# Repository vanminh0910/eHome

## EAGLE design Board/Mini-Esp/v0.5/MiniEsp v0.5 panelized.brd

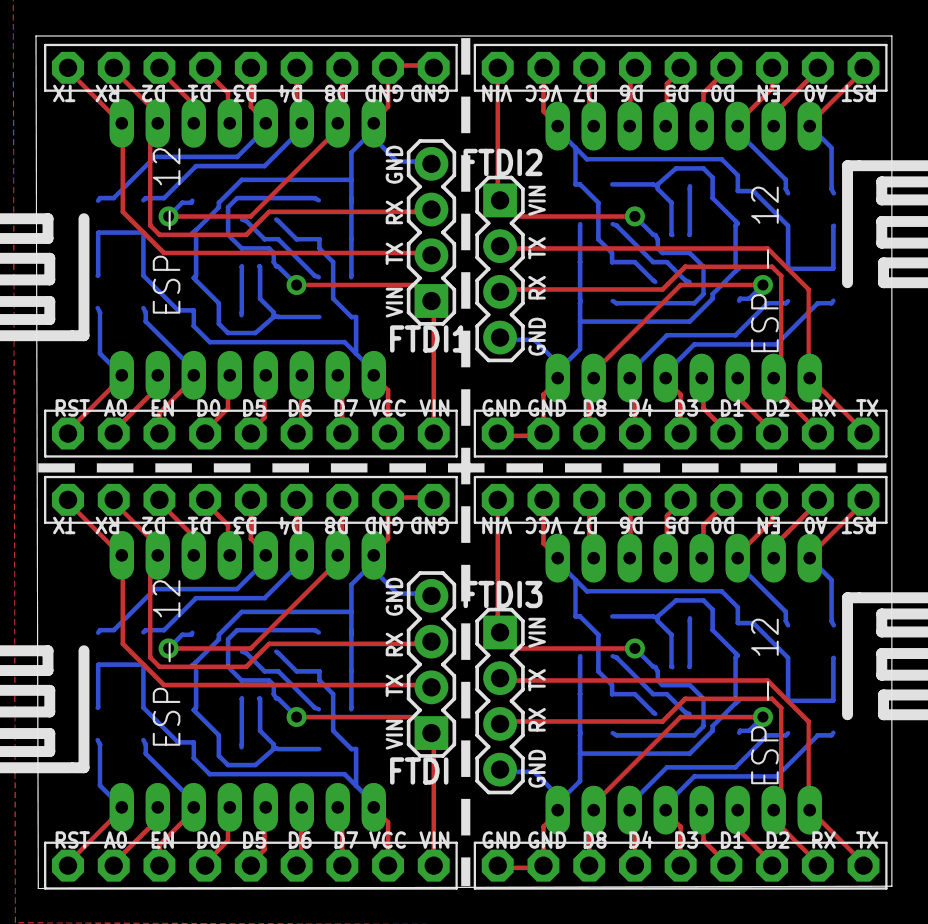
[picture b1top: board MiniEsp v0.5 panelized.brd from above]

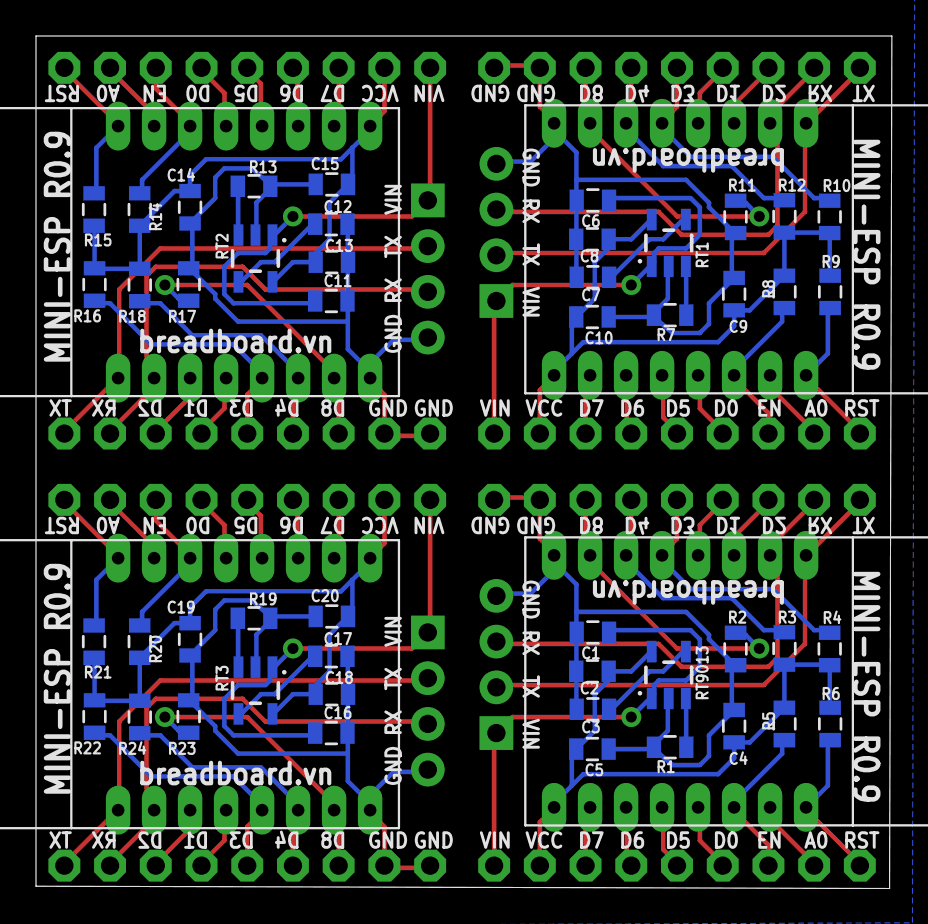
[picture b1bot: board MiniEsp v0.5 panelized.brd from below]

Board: 2 copper layers, 47.5 x 47.4 mm, 64 parts (48 on the bottom side), 76 nets.

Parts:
C1, C2, C6, C8, C11, C13, C16, C18: 1uF; 0805
C3, C7, C12, C17: 22nF; 0805
C4, C9, C14, C19: 10uF; 0805
C5, C10, C15, C20: 100nF; 0805
FTDI, FTDI1, FTDI2, FTDI3: 1X04
JP1, JP2, JP3, JP4, JP5, JP6, JP7, JP8: 1X09-BIG
R1, R7, R13, R19: 100K; 0805
R2, R3, R4, R5, R6, R8, R9, R10, R11, R12, R14, R15, R16, R17, R18, R20, R21, R22, R23, R24: 10K; 0805
RT1, RT2, RT3, RT9013: 3.3V/150mA; SOT23-5
U1, U2, U3, U4: ESP12

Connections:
A0: JP2.8, U2.ADC
A1: JP4.8, U1.ADC
A2: JP6.8, U3.ADC
A3: JP8.8, U4.ADC
BP: C3.1, RT9013.4
BP1: C7.1, RT1.4
BP2: C12.1, RT2.4
BP3: C17.1, RT3.4
D0: JP2.6, U2.GPIO16
D1: JP1.4, U2.GPIO5
D2: JP1.3, U2.GPIO4
D3: JP1.5, R4.1, U2.GPIO0
D4: JP1.6, R3.1, U2.GPIO2
D5: JP2.5, U2.GPIO14
D6: JP2.4, U2.GPIO12
D7: JP2.3, U2.GPIO13
D8: JP1.7, R2.1, U2.GPIO15
D9: JP3.3, U1.GPIO4
D10: JP3.4, U1.GPIO5
D11: JP3.5, R10.1, U1.GPIO0
D12: JP3.6, R12.1, U1.GPIO2
D13: JP3.7, R11.1, U1.GPIO15
D14: JP4.6, U1.GPIO16
D15: JP4.5, U1.GPIO14
D16: JP4.4, U1.GPIO12
D17: JP4.3, U1.GPIO13
D18: JP5.3, U3.GPIO4
D19: JP5.4, U3.GPIO5
D20: JP5.5, R16.1, U3.GPIO0
D21: JP5.6, R18.1, U3.GPIO2
D22: JP5.7, R17.1, U3.GPIO15
D23: JP6.6, U3.GPIO16
D24: JP6.5, U3.GPIO14
D25: JP6.4, U3.GPIO12
D26: JP6.3, U3.GPIO13
D27: JP7.3, U4.GPIO4
D28: JP7.4, U4.GPIO5
D29: JP7.5, R22.1, U4.GPIO0
D30: JP7.6, R24.1, U4.GPIO2
D31: JP7.7, R23.1, U4.GPIO15
D32: JP8.6, U4.GPIO16
D33: JP8.5, U4.GPIO14
D34: JP8.4, U4.GPIO12
D35: JP8.3, U4.GPIO13
EN: JP2.7, R5.1, U2.CH_PD
EN1: JP4.7, R8.1, U1.CH_PD
EN2: JP6.7, R14.1, U3.CH_PD
EN3: JP8.7, R20.1, U4.CH_PD
GND: C1.2, C2.2, C3.2, C4.2, C5.2, FTDI.4, JP1.8, JP1.9, R1.2, R2.2, RT9013.2, U2.GND
GND1: C6.2, C7.2, C8.2, C9.2, C10.2, FTDI1.4, JP3.8, JP3.9, R7.2, R11.2, RT1.2, U1.GND
GND2: C11.2, C12.2, C13.2, C14.2, C15.2, FTDI2.4, JP5.8, JP5.9, R13.2, R17.2, RT2.2, U3.GND
GND3: C16.2, C17.2, C18.2, C19.2, C20.2, FTDI3.4, JP7.8, JP7.9, R19.2, R23.2, RT3.2, U4.GND
LDO_EN: R1.1, RT9013.3
LDO_EN1: R7.1, RT1.3
LDO_EN2: R13.1, RT2.3
LDO_EN3: R19.1, RT3.3
RST: JP2.9, R6.1, U2.RESET
RST1: JP4.9, R9.1, U1.RESET
RST2: JP6.9, R15.1, U3.RESET
RST3: JP8.9, R21.1, U4.RESET
RX: FTDI.3, JP1.2, U2.RX
RX1: FTDI1.3, JP3.2, U1.RX
RX2: FTDI2.3, JP5.2, U3.RX
RX3: FTDI3.3, JP7.2, U4.RX
TX: FTDI.2, JP1.1, U2.TX
TX1: FTDI1.2, JP3.1, U1.TX
TX2: FTDI2.2, JP5.1, U3.TX
TX3: FTDI3.2, JP7.1, U4.TX
VCC: C2.1, C4.1, C5.1, JP2.2, R3.2, R4.2, R5.2, R6.2, RT9013.5, U2.VCC
VCC1: C8.1, C9.1, C10.1, JP4.2, R8.2, R9.2, R10.2, R12.2, RT1.5, U1.VCC
VCC2: C13.1, C14.1, C15.1, JP6.2, R14.2, R15.2, R16.2, R18.2, RT2.5, U3.VCC
VCC3: C18.1, C19.1, C20.1, JP8.2, R20.2, R21.2, R22.2, R24.2, RT3.5, U4.VCC
VIN: C1.1, FTDI.1, JP2.1, RT9013.1
VIN1: C6.1, FTDI1.1, JP4.1, RT1.1
VIN2: C11.1, FTDI2.1, JP6.1, RT2.1
VIN3: C16.1, FTDI3.1, JP8.1, RT3.1

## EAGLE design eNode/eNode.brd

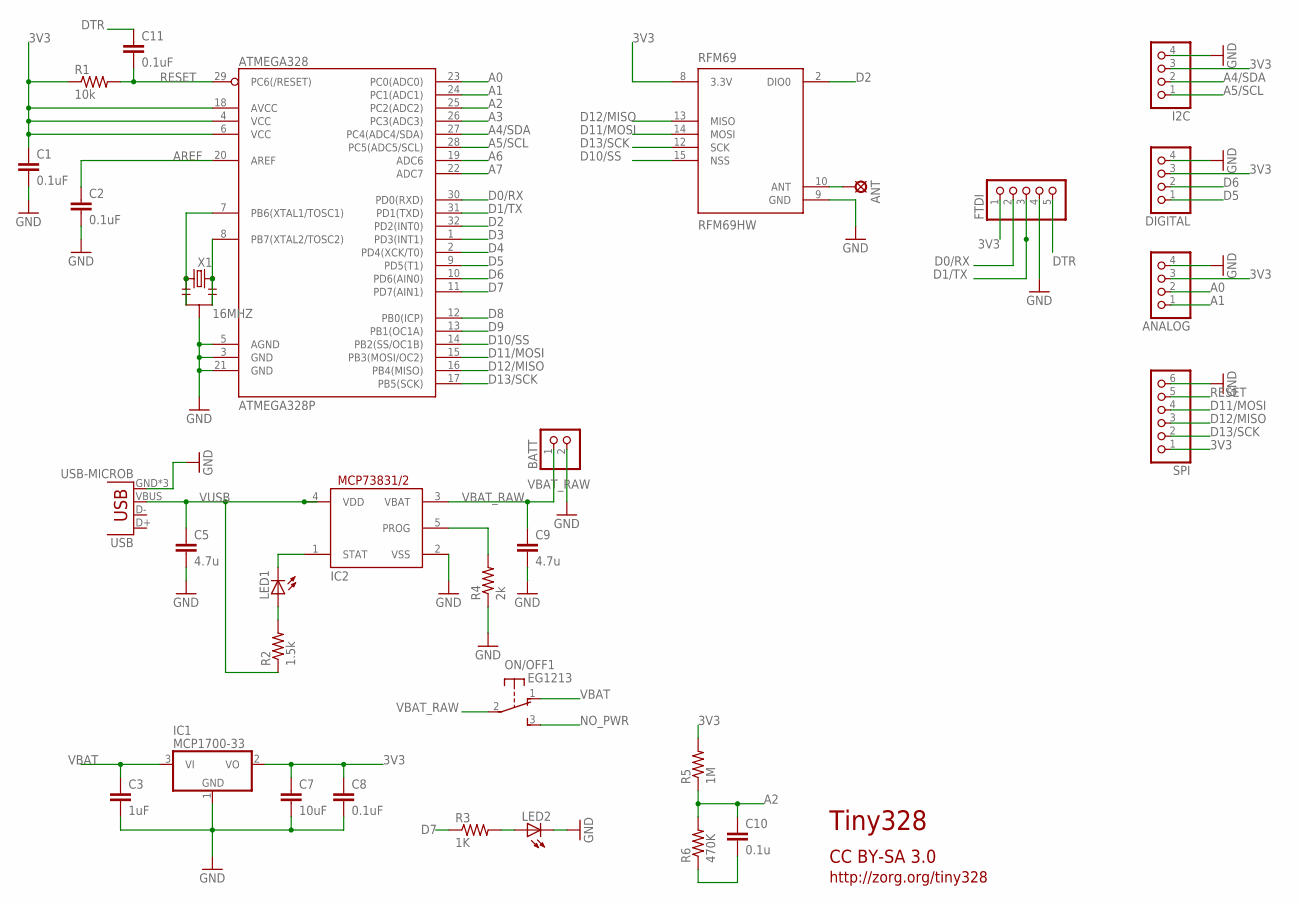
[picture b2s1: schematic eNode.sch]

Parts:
ANALOG: PINHD-1X4; 1X04
ANT: LSP10
ATMEGA328P: ATMEGA328; TQFP32-08
BATT: PINHD-1X2; 1X02
C1, C2, C8, C11: 0.1uF; 0603-CAP
C3: 1uF; 0603-CAP
C5, C9: 4.7u; 0603-CAP
C7: 10uF; 0603-CAP
C10: 0.1u; 0603-CAP
DIGITAL: PINHD-1X4; 1X04
FTDI: PINHD-1X5; 1X05
I2C: PINHD-1X4; 1X04
IC1: MCP1700-33; SOT23
IC2: MCP73831/OT; SOT23-5L
LED1, LED2: LEDCHIPLED_0603; CHIPLED_0603
ON/OFF: EG1213
R1: 10k; 0603-RES
R2: 1.5k; 0603-RES
R3: 1K; 0603-RES
R4: 2k; 0603-RES
R5: 1M; 0603-RES
R6: 470K; 0603-RES
RFM69: RFM69HW; RFM69W-XXXS2
SPI: PINHD-1X6; 1X06
USB: USB-MICROB
X1: 16MHZ; RESONATOR-SMD

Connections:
3V3: ANALOG.3, ATMEGA328P.4 (VCC), ATMEGA328P.6 (VCC), ATMEGA328P.18 (AVCC), C1.1, C7.1, C8.1, DIGITAL.3, FTDI.1, I2C.3, IC1.2 (VO), R1.1, R5.2, RFM69.8 (3.3V), SPI.1
A0: ANALOG.2, ATMEGA328P.23 (PC0(ADC0))
A1: ANALOG.1, ATMEGA328P.24 (PC1(ADC1))
A2: ATMEGA328P.25 (PC2(ADC2)), C10.1, R5.1, R6.2
A3: ATMEGA328P.26 (PC3(ADC3))
A4/SDA: ATMEGA328P.27 (PC4(ADC4/SDA)), I2C.2
A5/SCL: ATMEGA328P.28 (PC5(ADC5/SCL)), I2C.1
A6: ATMEGA328P.19 (ADC6)
A7: ATMEGA328P.22 (ADC7)
ANT: ANT.MP, RFM69.10 (ANT)
AREF: ATMEGA328P.20 (AREF), C2.1
D0/RX: ATMEGA328P.30 (PD0(RXD)), FTDI.2
D1/TX: ATMEGA328P.31 (PD1(TXD)), FTDI.3
D2: ATMEGA328P.32 (PD2(INT0)), RFM69.2 (DIO0)
D3: ATMEGA328P.1 (PD3(INT1))
D4: ATMEGA328P.2 (PD4(XCK/T0))
D5: ATMEGA328P.9 (PD5(T1)), DIGITAL.1
D6: ATMEGA328P.10 (PD6(AIN0)), DIGITAL.2
D7: ATMEGA328P.11 (PD7(AIN1)), R3.1
D8: ATMEGA328P.12 (PB0(ICP))
D9: ATMEGA328P.13 (PB1(OC1A))
D10/SS: ATMEGA328P.14 (PB2(SS/OC1B)), RFM69.15 (NSS)
D11/MOSI: ATMEGA328P.15 (PB3(MOSI/OC2)), RFM69.14 (MOSI), SPI.4
D12/MISO: ATMEGA328P.16 (PB4(MISO)), RFM69.13 (MISO), SPI.3
D13/SCK: ATMEGA328P.17 (PB5(SCK)), RFM69.12 (SCK), SPI.2
DTR: C11.1, FTDI.5
GND: ANALOG.4, ATMEGA328P.3 (GND), ATMEGA328P.5 (AGND), ATMEGA328P.21 (GND), BATT.2, C1.2, C2.2, C3.2, C5.2, C7.2, C8.2, C9.2, DIGITAL.4, FTDI.4, I2C.4, IC1.1 (GND), IC2.2 (VSS), LED2.C, R4.1, RFM69.9 (GND), SPI.6, USB.GND, USB.MT1 (GND), USB.MT2 (GND), X1.2
unnamed: LED1.A, R2.2
unnamed: ATMEGA328P.7 (PB6(XTAL1/TOSC1)), X1.1
unnamed: ATMEGA328P.8 (PB7(XTAL2/TOSC2)), X1.3
unnamed: C10.2, R6.1
unnamed: LED2.A, R3.2
NO_PWR: ON/OFF.3 (S)
PROG: IC2.5 (PROG), R4.2
RESET: ATMEGA328P.29 (PC6(/RESET)), C11.2, R1.2, SPI.5
STAT: IC2.1 (STAT), LED1.C
VBAT: C3.1, IC1.3 (VI), ON/OFF.1 (O)
VBAT_RAW: BATT.1, C9.1, IC2.3 (VBAT), ON/OFF.2
VUSB: C5.1, IC2.4 (VDD), R2.1, USB.VBUS

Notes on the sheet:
Tiny328
CC BY-SA 3.0
http://zorg.org/tiny328

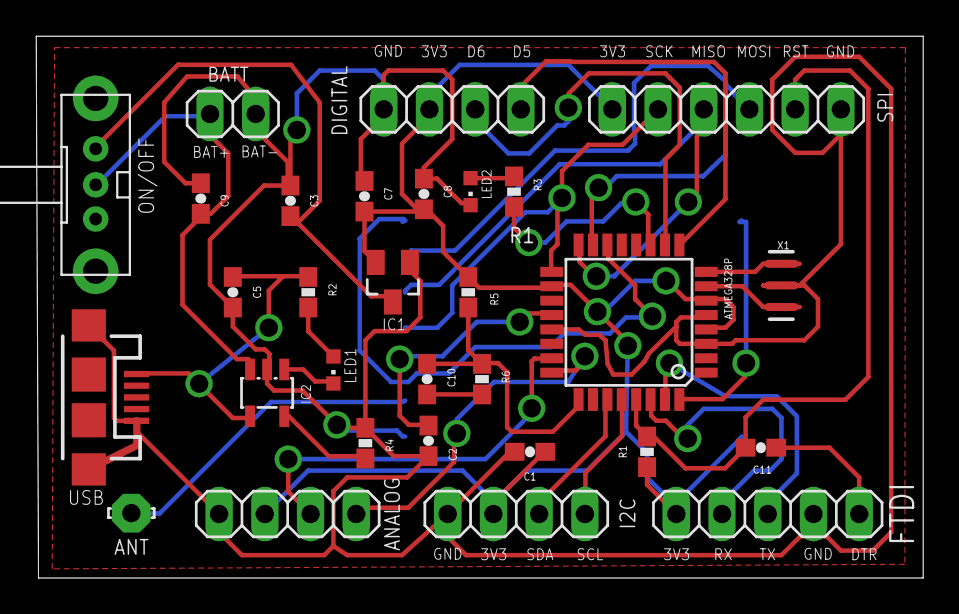
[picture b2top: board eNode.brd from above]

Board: 2 copper layers, 49.3 x 30.1 mm, 31 parts (1 on the bottom side), 31 nets.

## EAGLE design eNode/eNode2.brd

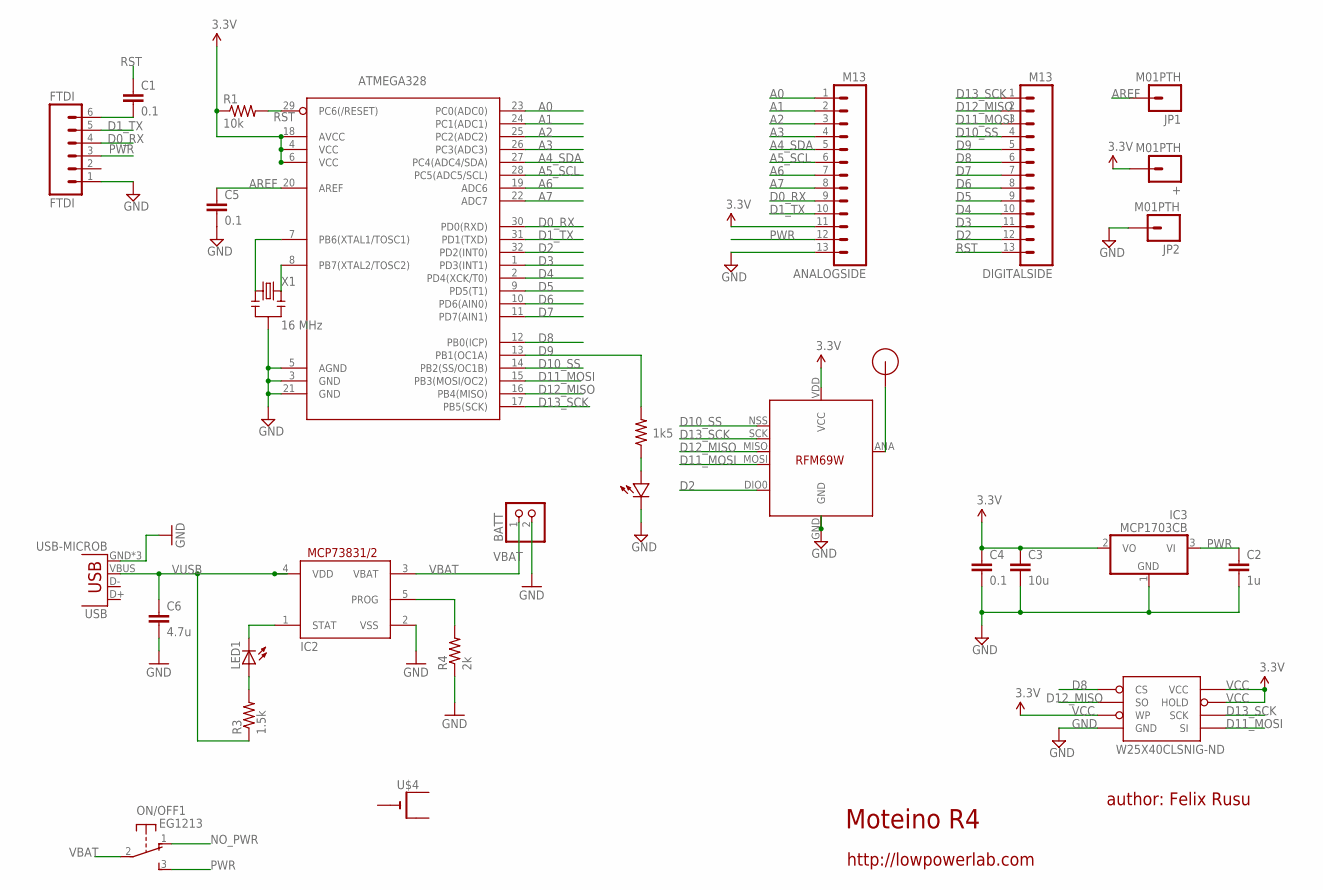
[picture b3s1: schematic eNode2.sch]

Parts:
+: M01PTH; 1X01
ANALOGSIDE: M13; 1X13
ATMEGA328: ATMega-328; TQFP32-08
BATT: PINHD-1X2; 1X02
C1, C4, C5: 0.1; 0603-CAP
C2: 1u; 0603-CAP
C3: 10u; 0805-CAP
C6: 4.7u; 0603-CAP
DIGITALSIDE: M13; 1X13
FTDI: FTDI; 1X06
IC2: MCP73831/OT; SOT23-5L
IC3: MCP1703CB; SOT23
JP1, JP2: M01PTH; 1X01
LED1: LEDCHIPLED_0603; CHIPLED_0603
ON/OFF: EG1213
R1: 10k; 0603-RES
R2: 1k5; 0603-RES
R3: 1.5k; 0603-RES
R4: 2k; 0603-RES
U$1: RFM12B_ANTENNA; RFM12B-ANTENNA
U$2: LED0603; 0603-LED
U$4: CR2032THM; CR2032-THRU
U$5: RFM69; RFM69W-MINPADS
USB: USB-MICROB
W25X40CLSNIG-ND: AT25F512BWIDE_5.3MM; SO08WIDE
X1: 16 MHz; RESONATOR-SMD

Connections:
A0: ANALOGSIDE.1, ATMEGA328.23 (PC0(ADC0))
A1: ANALOGSIDE.2, ATMEGA328.24 (PC1(ADC1))
A2: ANALOGSIDE.3, ATMEGA328.25 (PC2(ADC2))
A3: ANALOGSIDE.4, ATMEGA328.26 (PC3(ADC3))
A4_SDA: ANALOGSIDE.5, ATMEGA328.27 (PC4(ADC4/SDA))
A5_SCL: ANALOGSIDE.6, ATMEGA328.28 (PC5(ADC5/SCL))
A6: ANALOGSIDE.7, ATMEGA328.19 (ADC6)
A7: ANALOGSIDE.8, ATMEGA328.22 (ADC7)
AREF: ATMEGA328.20 (AREF), C5.1, JP1.1
D0_RX: ANALOGSIDE.9, ATMEGA328.30 (PD0(RXD)), FTDI.4
D1_TX: ANALOGSIDE.10, ATMEGA328.31 (PD1(TXD)), FTDI.5
D2: ATMEGA328.32 (PD2(INT0)), DIGITALSIDE.12, U$5.DIO0
D3: ATMEGA328.1 (PD3(INT1)), DIGITALSIDE.11
D4: ATMEGA328.2 (PD4(XCK/T0)), DIGITALSIDE.10
D5: ATMEGA328.9 (PD5(T1)), DIGITALSIDE.9
D6: ATMEGA328.10 (PD6(AIN0)), DIGITALSIDE.8
D7: ATMEGA328.11 (PD7(AIN1)), DIGITALSIDE.7
D8: ATMEGA328.12 (PB0(ICP)), DIGITALSIDE.6, W25X40CLSNIG-ND.1 (CS)
D9: ATMEGA328.13 (PB1(OC1A)), DIGITALSIDE.5, R2.2
D10_SS: ATMEGA328.14 (PB2(SS/OC1B)), DIGITALSIDE.4, U$5.NSS (SEL)
D11_MOSI: ATMEGA328.15 (PB3(MOSI/OC2)), DIGITALSIDE.3, U$5.MOSI, W25X40CLSNIG-ND.5 (SI)
D12_MISO: ATMEGA328.16 (PB4(MISO)), DIGITALSIDE.2, U$5.MISO, W25X40CLSNIG-ND.2 (SO)
D13_SCK: ATMEGA328.17 (PB5(SCK)), DIGITALSIDE.1, U$5.SCK, W25X40CLSNIG-ND.6 (SCK)
GND: ANALOGSIDE.13, ATMEGA328.3 (GND), ATMEGA328.5 (AGND), ATMEGA328.21 (GND), BATT.2, C2.2, C3.2, C4.2, C5.2, C6.2, FTDI.1, IC2.2 (VSS), IC3.1 (GND), JP2.1, R4.1, U$2.MINUS, U$5.GND, USB.GND, USB.MT1 (GND), USB.MT2 (GND), W25X40CLSNIG-ND.4 (GND), X1.2
unnamed: ATMEGA328.7 (PB6(XTAL1/TOSC1)), X1.1
unnamed: R2.1, U$2.PLUS
unnamed: U$1.P$1, U$5.ANA (ANT)
unnamed: LED1.A, R3.2
unnamed: C1.2, FTDI.6
unnamed: ATMEGA328.8 (PB7(XTAL2/TOSC2)), X1.3
NO_PWR: ON/OFF.1 (O)
PROG: IC2.5 (PROG), R4.2
PWR: ANALOGSIDE.12, C2.1, FTDI.3, IC3.3 (VI), ON/OFF.3 (S)
RST: ATMEGA328.29 (PC6(/RESET)), C1.1, DIGITALSIDE.13, R1.2
STAT: IC2.1 (STAT), LED1.C
VBAT: BATT.1, IC2.3 (VBAT), ON/OFF.2
VCC: +.1, ANALOGSIDE.11, ATMEGA328.4 (VCC), ATMEGA328.6 (VCC), ATMEGA328.18 (AVCC), C3.1, C4.1, IC3.2 (VO), R1.1, U$5.VDD (VCC), W25X40CLSNIG-ND.3 (WP), W25X40CLSNIG-ND.7 (HOLD), W25X40CLSNIG-ND.8 (VCC)
VUSB: C6.1, IC2.4 (VDD), R3.1, USB.VBUS

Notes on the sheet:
Moteino R4
author: Felix Rusu
http://lowpowerlab.com

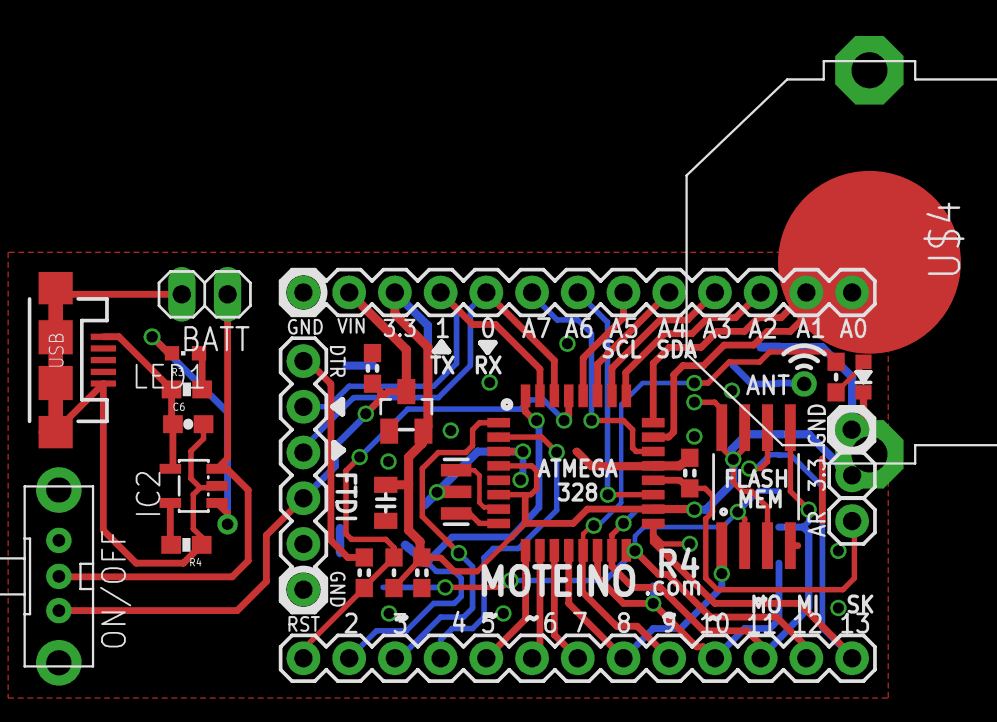
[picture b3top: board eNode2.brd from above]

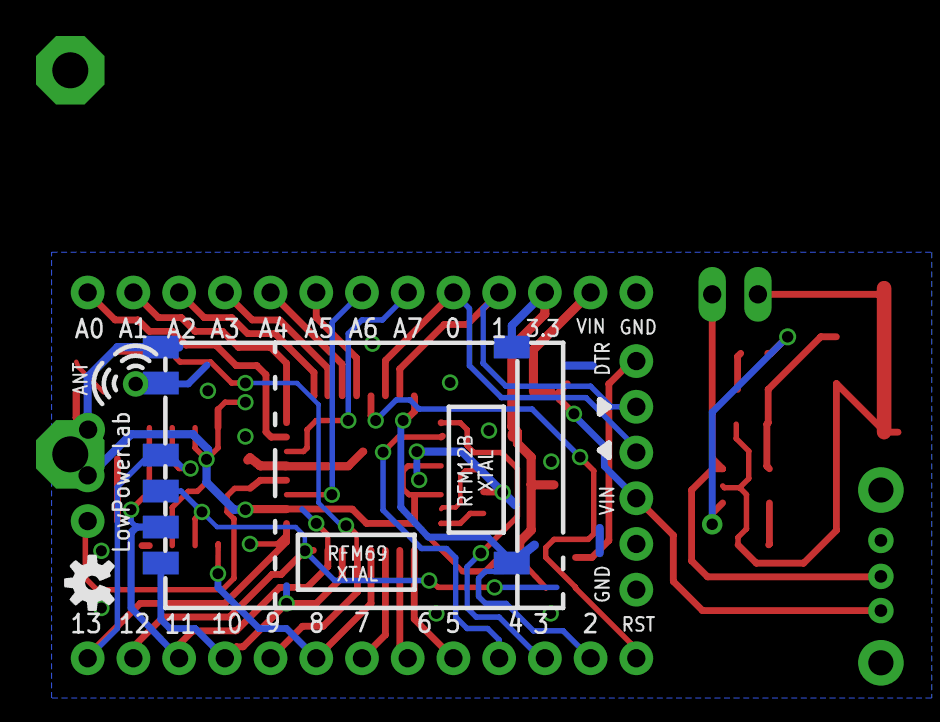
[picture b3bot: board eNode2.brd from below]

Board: 2 copper layers, 30 parts (2 on the bottom side), 37 nets.

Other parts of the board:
U$3: OSHW-LOGO-S

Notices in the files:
parts and their libraries:
SparkFun-Passives: Licensing: Creative Commons ShareAlike 4.0 International - https://creativecommons.org/licenses/by-sa/4.0
SparkFun-DigitalIC: Licensing: CC v3.0 Share-Alike You are welcome to use this library for commercial purposes.
